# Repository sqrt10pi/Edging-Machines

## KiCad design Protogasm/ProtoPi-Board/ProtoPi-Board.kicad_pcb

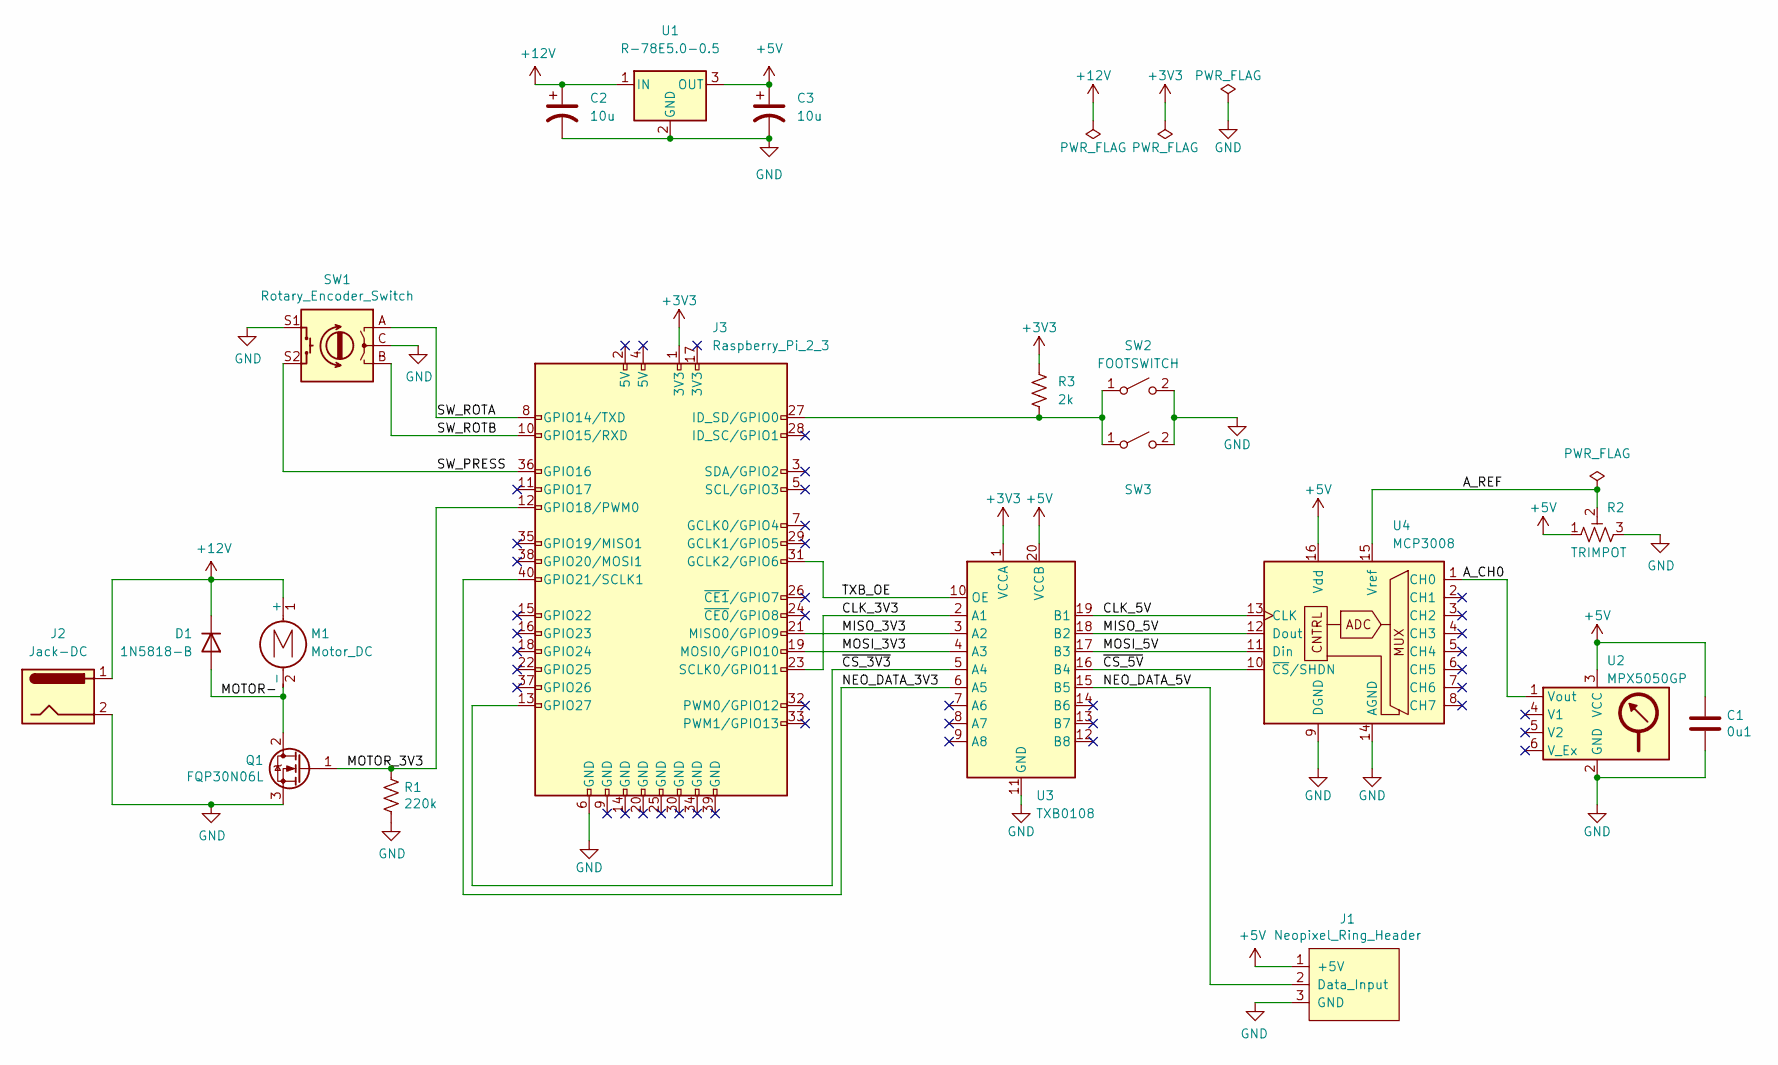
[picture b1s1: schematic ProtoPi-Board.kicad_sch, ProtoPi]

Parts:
C1: 0u1; C_Disc_D5.0mm_W2.5mm_P2.50mm
C2, C3: 10u; CP_Radial_D5.0mm_P2.50mm
D1: 1N5818-B; D_A-405_P7.62mm_Horizontal
J1: Neopixel_Ring_Header; Neopixel_Ring_WirePins
J2: Jack-DC; 2.1mm DC Barrel Jack
J3: Raspberry_Pi_2_3; Raspberry_Pi_4_Model_B
M1: Motor_DC; Motor_DC_WirePins
Q1: FQP30N06L; TO-220-3_Horizontal_TabDown
R1: 220k; R_Axial_DIN0207_L6.3mm_D2.5mm_P7.62mm_Horizontal
R2: TRIMPOT; uxcell_TRIMPOT
R3: 2k; R_Axial_DIN0207_L6.3mm_D2.5mm_P7.62mm_Horizontal
SW1: Rotary_Encoder_Switch; RotaryEncoder_Alps_EC12E-Switch_Vertical_H20mm
SW2: FOOTSWITCH; Motor_DC_WirePins
SW3: (no value)
U1: R-78E5.0-0.5; Converter_DCDC_RECOM_R-78E-0.5_THT
U2: MPX5050GP
U3: TXB0108; TXB0108-Adafruit
U4: MCP3008; DIP-16_W7.62mm

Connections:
+3V3: J3.1 (3V3), R3.1, U3.1 (VCCA)
+5V: C1.1, C3.1, J1.1 (+5V), R2.1, U1.3 (OUT), U2.3 (VCC), U3.20 (VCCB), U4.16 (Vdd)
+12V: C2.1, D1.1 (K), J2.1, M1.1 (+), U1.1 (IN)
/A_CH0: U2.1 (Vout), U4.1 (CH0)
/A_REF: R2.2, U4.15 (Vref)
/CLK_3V3: J3.23 (SCLK0/GPIO11), U3.2 (A1)
/CLK_5V: U3.19 (B1), U4.13 (CLK)
/MISO_3V3: J3.21 (MISO0/GPIO9), U3.3 (A2)
/MISO_5V: U3.18 (B2), U4.12 (Dout)
/MOSI_3V3: J3.19 (MOSI0/GPIO10), U3.4 (A3)
/MOSI_5V: U3.17 (B3), U4.11 (Din)
/MOTOR-: D1.2 (A), M1.2 (-), Q1.2 (D)
/MOTOR_3V3: J3.12 (GPIO18/PWM0), Q1.1 (G), R1.1
/NEO_DATA_3V3: J3.40 (GPIO21/SCLK1), U3.6 (A5)
/NEO_DATA_5V: J1.2 (Data_Input), U3.15 (B5)
/SW_PRESS: J3.36 (GPIO16), SW1.S2
/SW_ROTA: J3.8 (GPIO14/TXD), SW1.A
/SW_ROTB: J3.10 (GPIO15/RXD), SW1.B
/TXB_OE: J3.31 (GCLK2/GPIO6), U3.10 (OE)
/~CS_3V3: J3.13 (GPIO27), U3.5 (A4)
/~CS_5V: U3.16 (B4), U4.10 (~CS/SHDN)
GND: C1.2, C2.2, C3.2, J1.3 (GND), J2.2, J3.6 (GND), Q1.3 (S), R1.2, R2.3, SW1.C, SW1.S1, SW2.2 (B), SW3.2 (B), U1.2 (GND), U2.2 (GND), U3.11 (GND), U4.9 (DGND), U4.14 (AGND)
unnamed: J3.27 (ID_SD/GPIO0), R3.2, SW2.1 (A), SW3.1 (A)

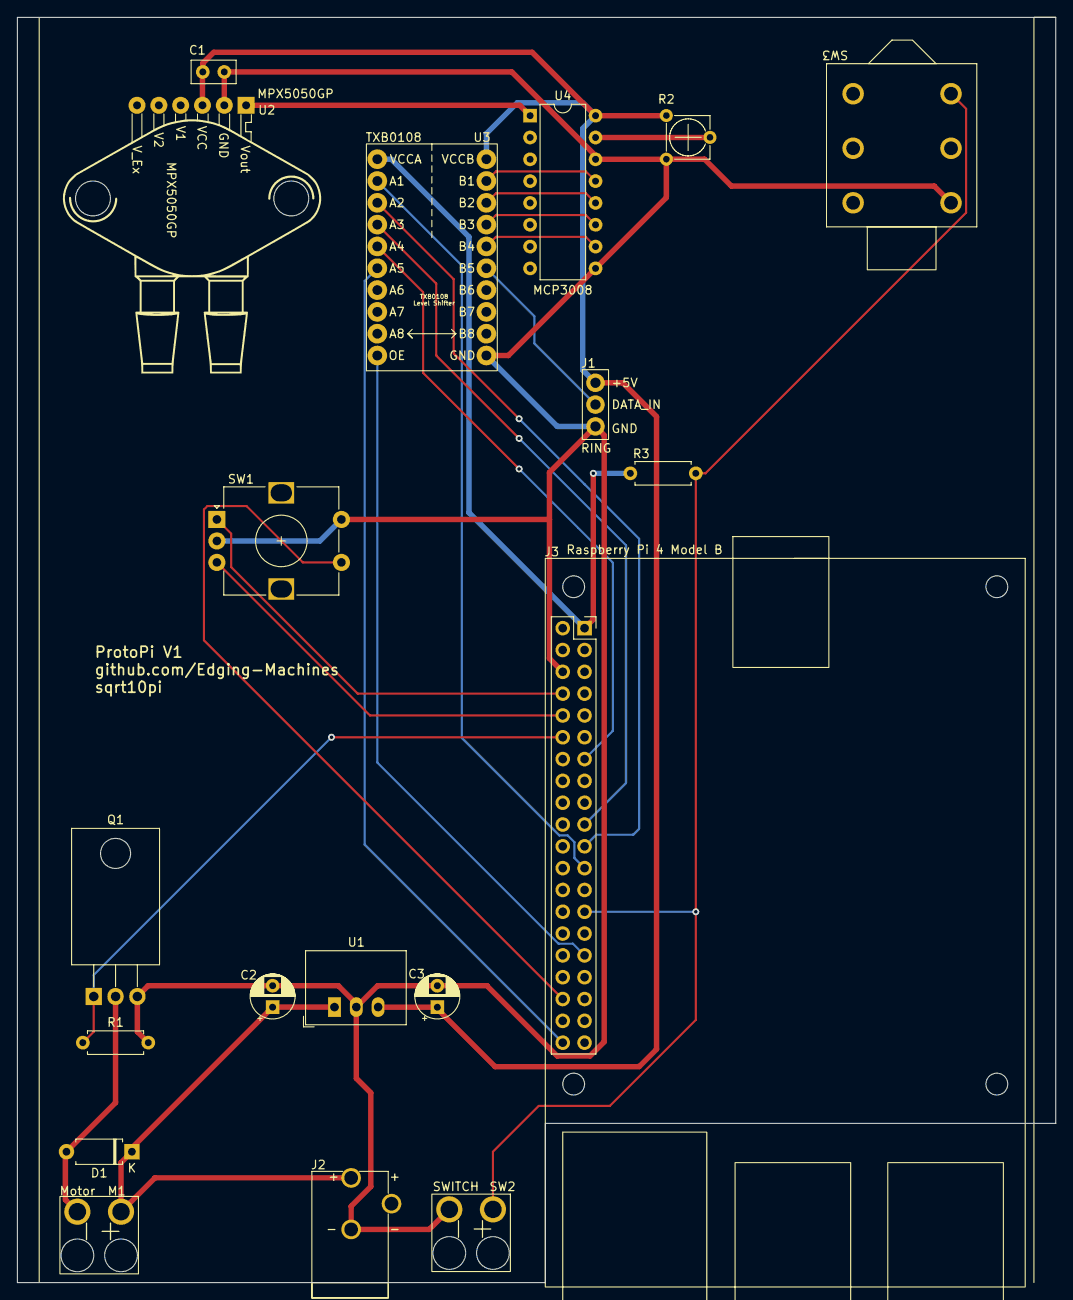
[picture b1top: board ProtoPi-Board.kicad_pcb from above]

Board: 2 copper layers, 120.9 x 147.3 mm, 19 parts (0 on the bottom side), 23 nets.

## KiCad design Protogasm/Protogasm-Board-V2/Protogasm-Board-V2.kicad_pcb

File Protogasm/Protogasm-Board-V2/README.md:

# Protogasm Board V2

## Changelog

- Recreated the PCB from the Protogasm-Board folder in Kicad with only very minor changes.
- The vast majority of components are exactly lined up with the existing board. I overlaid the existing board's Gerbers with the gerbers of the remake and adjusted positions until stuff matched exactly.
- The general components C1, D1, SW1, and R1 have slightly different footprints because I was using the Kicad builtin footprints. They aren't pixel perfect but still overall in the same positions.
- I didn't want to just have loose pins for the motor connections and neopixel connections so I created actual components for them, this means I had to move them so that's one thing that has changed significantly in this board.
- Added the Arduino mounting holes, mostly so that it will be easier to test alignment of this board and the case.
- Overall, the idea is that if someone wants to change the Protogasm-Board but doesn't want the other changes that I'd like to make, they could start from this commit.

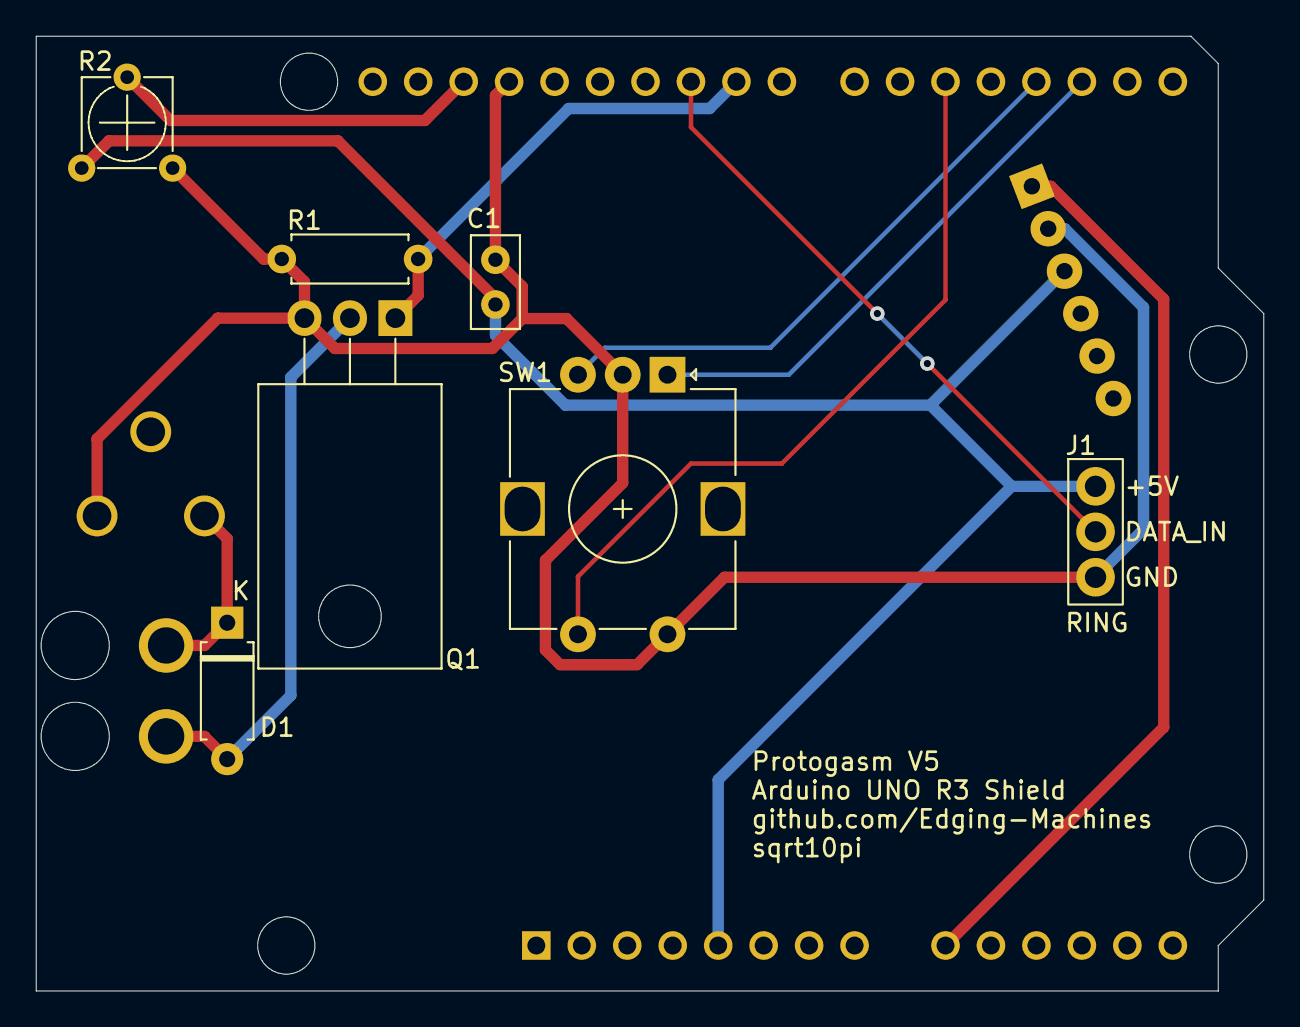
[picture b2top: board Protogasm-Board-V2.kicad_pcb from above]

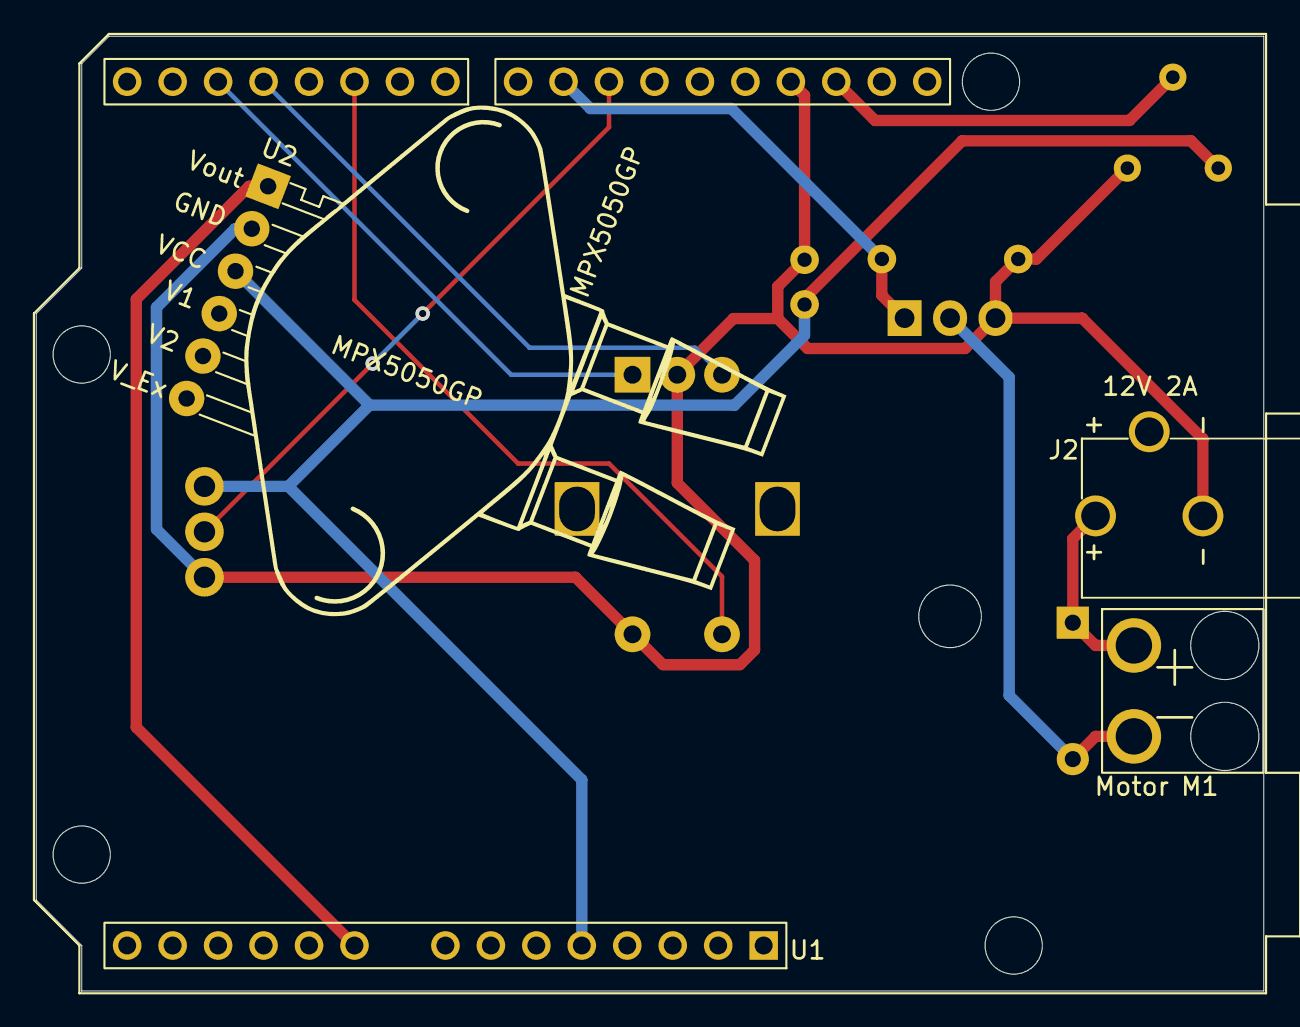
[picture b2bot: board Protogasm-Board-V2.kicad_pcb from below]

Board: 2 copper layers, 68.6 x 53.3 mm, 11 parts (4 on the bottom side), 11 nets.

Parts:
C1: 0u1; C_Disc_D5.0mm_W2.5mm_P2.50mm
D1: 1N5818-B; D_A-405_P7.62mm_Horizontal
J1: Neopixel_Ring_Header; Neopixel_Ring_WirePins
J2: Jack-DC; 2.1mm DC Barrel Jack
M1: Motor_DC; Motor_DC_WirePins
Q1: FQP30N06L; TO-220-3_Horizontal_TabDown
R1: 220k; R_Axial_DIN0207_L6.3mm_D2.5mm_P7.62mm_Horizontal
R2: TRIMPOT; uxcell_TRIMPOT
SW1: Rotary_Encoder_Switch; RotaryEncoder_Alps_EC12E-Switch_Vertical_H20mm
U1: Arduino_UNO_R3; Arduino_UNO_R3_WithMountingHoles
U2: MPX5050GP

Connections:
+5V: C1.1, J1.1 (+5V), R2.1, U1.5 (+5V), U2.3 (VCC)
+12V: D1.1 (K), J2.1, M1.1 (+)
/A0: U1.9 (A0), U2.1 (Vout)
/AREF: R2.2, U1.30 (AREF)
/D2: SW1.A, U1.17 (D2)
/D3: SW1.B, U1.18 (D3)
/D5: SW1.S2, U1.20 (D5)
/D9: Q1.1 (G), R1.1, U1.24 (D9)
/D10: J1.2 (Data_Input), U1.25 (D10)
/MOTOR-: D1.2 (A), M1.2 (-), Q1.2 (D)
GND: C1.2, J1.3 (GND), J2.2, Q1.3 (S), R1.2, R2.3, SW1.C, SW1.S1, U1.29 (GND), U2.2 (GND)

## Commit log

2022-01-16 Complete the schematic
2022-01-28 Protogasm-Board-V2.sch verified to match Protogasm_Board_Schematic.png
2022-01-28 Convert to Kicad6
2022-01-28 Assign a few footprints (although we need to make some custom ones
2022-01-28 Set up custom footprints
2022-01-30 Finished the custom footprints
2022-01-30 Reroute board
2022-01-30 Component placements match V1 exactly
2022-01-30 Finalize protogasm board V2 (the basic remake)
2022-01-30 Generate gerbers
2022-01-30 Place components pretty close to where they should be
2022-01-30 Move SW1 to line up with case
2022-01-30 Move components so that SW1 and MPX5050GP will fit
2022-01-30 Finalize Protogasm-Board-V3, with properly placed MPX and SW1
2022-01-30 Get symbols working again in Kicad6
2022-01-30 Update schematic for V4
2022-01-30 Protogasm V4 - with DCDC converter and dedicated power jack
2022-03-20 Start protopi folder
